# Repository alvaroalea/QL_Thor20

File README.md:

# THOR PC Computer (Compatible with Sinclair Ql)
A reverse engineering exercice using the Sinclair QL compatible Thor-20 Computer as target

Licensed under Cern OHL-S - https://ohwr.org/cern_ohl_s_v2.txt

## WARNING: DO NOT USE THIS PROJECT IS NOT TESTED AND MISSING THINGS
This is not a functional item, it's only a exercice of reverse engineering to reinforce my skills in Kicad EDA Software.

## History

With the end of the comercial life of the Sinclair QL, other companies fill the gap, CST create several models of the Thor computer.

The subject of this project is a interesting one, using old stock of original QL boards, and a re-edition of several of the previous expansion board together with a fancy desktop case to make a enhaced QL Computer, so the Thor consist of:

- The Original QL Board
- The RAM + ROM expansion board board (512Kb of RAM)
- The CST Floppy Disk Interface with 1 or 2 3 1/2" floppy drivers
- The CST SCSI Disk Interface
- The mICE mouse + desktop software solution
- A RTC implementation
- A fancy box
- A upgraded in-box power supply
- Standar PC XT Interface

This was called Thor PC, Thor 1 or Thor 8, depend of the sources of information, there are 3 version available, 1F, 2F, 2WF depend on the number of floppys and Winchister hard disc or not, 1F,2F do not incorporate the IC of the SCSI interface, but can be upgraded later.

Later, CST upgrade it and made the Thor 20 and Thor 21, this was Thor 1 with a CPU-Addon card, that include a 68020 CPU at 12 or 16Mhz, and a 68881 FPU math coprocesor.

Unfortunately, the use of the original QL board, and the RAM in 8bits, cause this board to be only twice the speed of the original QL, while a Gold Card provide the same with twice the ram, and the Super Gold Card provide 4 times the speed of the QL, 4Mb of RAM using the same microprocessor.

## The Project

I will try to recreate all the hardware, and document in a proper way everything I can get of the Thor Computer, up to day there is only some low resolution pictures, a bad scanned service manual, and a dump of some of the ROMs of the computer.

## Technical Information

### Power Supply
The thor 20 come with a IEC C13 socket in the back, and a secondary C14 (for the monitor) a switch shall power on/off both the computer and monitor.

Internally a power supply rated to 30W is used for the system. it provide:
- +5Vdc probably at 3A (for everything)
- +12Vdc probably at 1A (for QL, hard disc and floppy)
- -12Vdc probably at 250mA (for the serial ports of the QL)

a MeanWell PT-45A is probably the good replacement ( https://www.meanwell-web.com/en-gb/ac-dc-triple-output-open-frame-power-supply-output-pt--45a ).

### SCSI Upgrade Kit
To upgrade the Thor 1F or 2F to 2WF a kit of IC11,IC12,IC13 and IC15 can be installed to enable the SCSI interface.

### Memory Mapping

- 0000-0048 Sinclair QL ROM
- 0049-0064 Free for ROM Cartridge Slot
- 0065-0096 Internal 32Kb I/O
- 0097-0128 Free but reserved for I/O
- 0129-0256 Internal QL 128K RAM including Video ram
- 0257-0768 CST 512 Kb Expansion RAM
- 0769-0832 Free 64Kb for external expansion interfaces
- 0833-0999 5x32Kb + 1x8Kb expasion ROM
- 1000-1024 CST Expansion I/O

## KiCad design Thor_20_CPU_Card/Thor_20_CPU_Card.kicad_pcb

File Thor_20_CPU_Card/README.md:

# CST Thor - 68020 CPU Board.

(C) 2023 Alvaro Alea Fernandez

License under: CERN Open Hardware Licence Version 2 - Strongly Reciprocal

https://ohwr.org/cern_ohl_s_v2.txt

This board is the "overdrive" board that shall upgrade the 68008 processor of the Sinclair QL to a 68020 one.

THIS BOARD HAS NOT BEEN TESTED!! Use at your own risk.

##Information

There at least 1 GAL and 1 ROM with ecuations or contens are missing so it not usable at present.

* Get energy from diferent a power supply.
* Dimensions are not checked, there is mismatch in pictures.
* Schematic is not pretty, but is enought to be able to do the PCB.

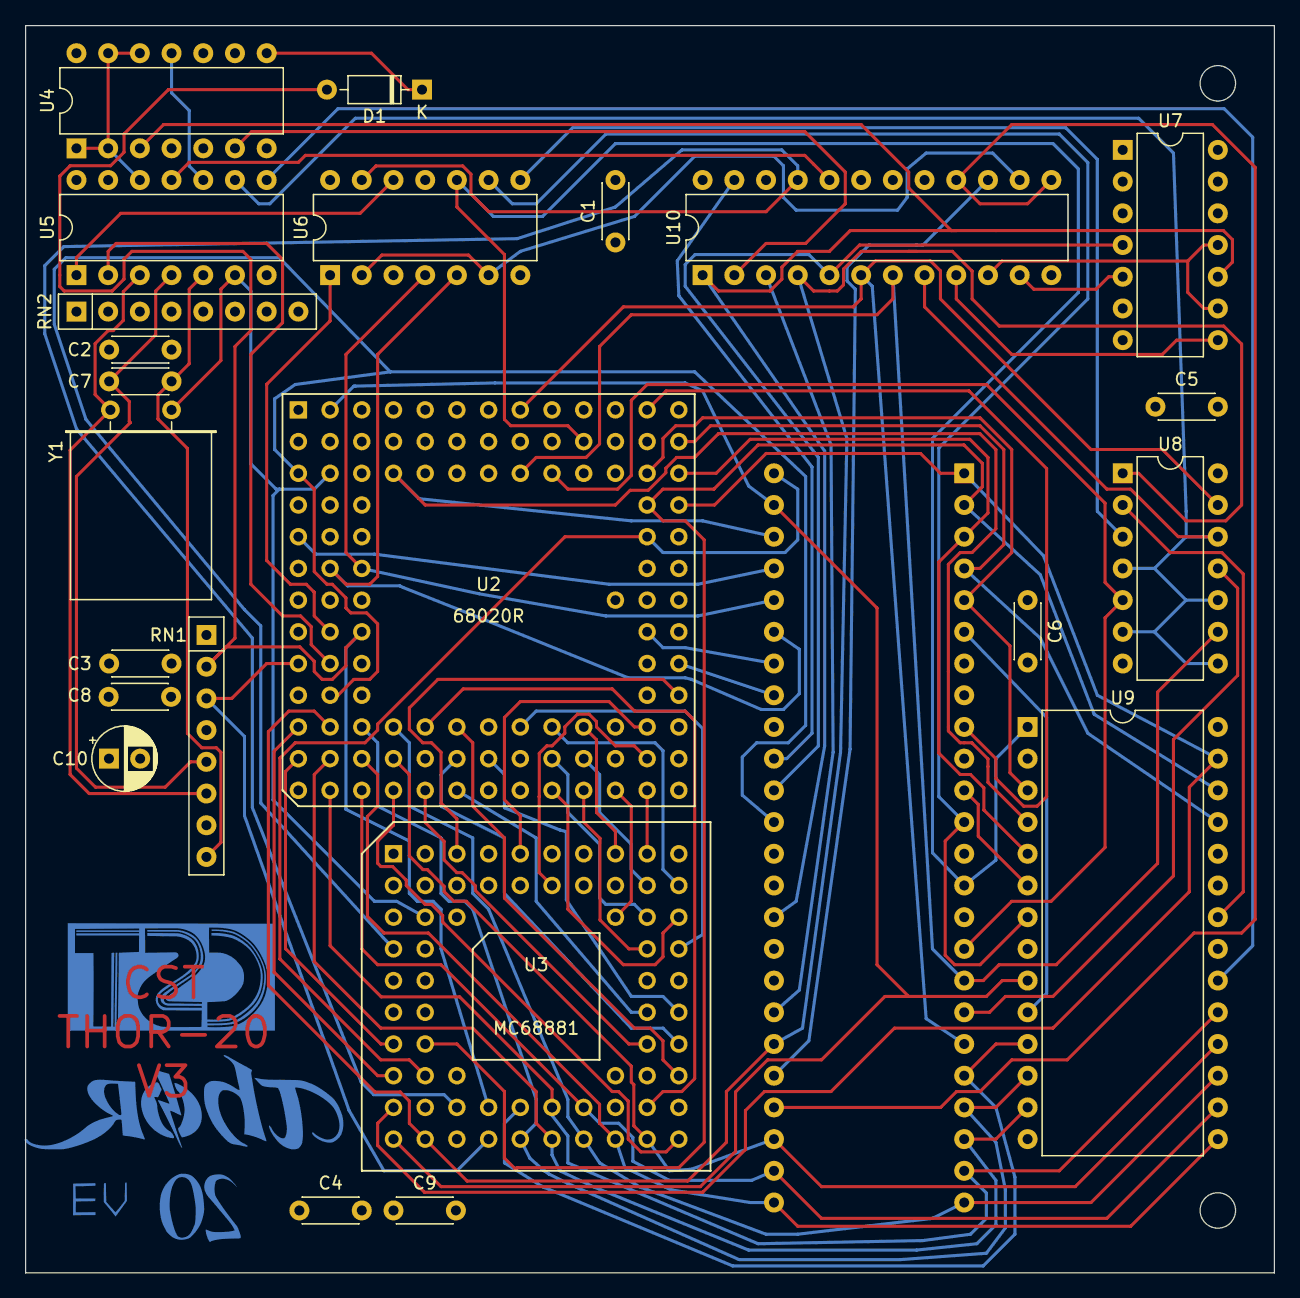
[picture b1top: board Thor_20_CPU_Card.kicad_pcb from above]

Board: 4 copper layers, 100.0 x 99.9 mm, 24 parts (1 on the bottom side), 92 nets.

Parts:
C1, C2, C3, C4, C5, C6, C7, C8, C9: C; C_Disc_D4.3mm_W1.9mm_P5.00mm
C10: C_Polarized; CP_Radial_D5.0mm_P2.50mm
D1: BAT85; D_DO-35_SOD27_P7.62mm_Horizontal
RN1, RN2: R_Pack04_SIP_Split; R_Array_SIP8
U1: 68008D; DIP-48_W15.24mm
U2: 68020R; PGA114
U3: MC68881; PGA68
U4: 74LS74; DIP-14_W7.62mm
U5: 74LS04; DIP-14_W7.62mm
U6: 74LS11; DIP-14_W7.62mm
U7: 74LS290; DIP-14_W7.62mm
U8: 74LS05; DIP-14_W7.62mm
U9: W27C512; DIP-28_W15.24mm
U10: PAL20R4; DIP-24_W7.62mm
Y1: 12Mhz; Crystal_HC18-U_Horizontal

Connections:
+5V: C1.1, C2.1, C3.1, C4.1, C5.1, C6.1, C8.1, C10.1, RN1.1 (R1.1), RN1.4 (R2.2), RN2.2 (R1.2), U1.13 (VCC), U2.A1 (BGACK), U2.A9 (VCC), U2.B3 (BR), U2.D1 (VCC), U2.D2 (VCC), U2.D3 (VCC), U2.E3 (VCC), U2.G11 (VCC), U2.G13 (VCC), U2.H1 (CDIS), U2.J12 (IPL0), U2.M8 (VCC), U2.N8 (VCC), U2.N13 (VCC), U3.A1 (VDD), U3.B1 (VDD), U3.B8 (VDD), U3.E2 (VDD), U3.E9 (VDD), U3.F1 (~SIZE), U3.H3 (A0), U3.H8 (VDD), U3.J2 (VDD), U4.4 (~S), U4.10 (~S), U4.14 (VCC), U5.14 (VCC), U6.11, U6.14 (VCC), U7.14 (VCC), U8.14 (VCC), U9.28 (VCC), U10.24 (VCC)
/A0: U1.46 (A0), U2.C4 (A0), U9.4 (A6)
/A1: U1.47 (A1), U2.A2 (A1), U3.K1 (A1), U9.9 (A1)
/A2: U1.48 (A2), U2.E12 (A2), U3.H2 (A2), U9.8 (A2)
/A3: U1.1 (A3), U2.D13 (A3), U3.J1 (A3), U9.27 (A14)
/A4: U1.2 (A4), U2.D12 (A4), U3.G2 (A4), U9.26 (A13)
/A5: U1.3 (A5), U2.C13 (A5), U9.5 (A5)
/A6: U1.4 (A6), U2.B13 (A6), U9.25 (A8)
/A7: U1.5 (A7), U2.C12 (A7), U9.3 (A7)
/A8: U1.6 (A8), U2.A13 (A8), U9.10 (A0)
/A9: U1.7 (A9), U2.C11 (A9), U9.24 (A9)
/A10: U1.8 (A10), U2.B12 (A10), U9.21 (A10)
/A11: U1.9 (A11), U2.A12 (A11), U9.23 (A11)
/A12: U1.10 (A12), U2.C10 (A12), U9.2 (A12)
/A13: U1.11 (A13), U2.B11 (A13), U9.6 (A4)
/A14: U1.12 (A14), U2.A11 (A14), U6.9, U9.7 (A3)
/A15: U1.14 (A15), U2.B10 (A15), U6.10, U9.1 (A15)
/A16: U1.16 (A16), U2.C9 (A16), U8.5
/A17: U1.17 (A17), U2.C8 (A17), U8.9, U10.7 (I7)
/A18: U1.18 (A18), U2.B8 (A18), U8.11
/A19: U1.19 (A19), U2.A8 (A19), U8.13, U10.6 (I6)
/ACK2: U5.11, U10.20 (I04)
/AS: U2.L1 (AS), U3.H1 (~AS), U5.13
/AS2: U4.6 (~Q), U10.2 (I2)
/AS_68K8: U1.28 (AS), U10.13 (I12), U10.16 (IO8)
/AVEC: U2.H2 (AVEC), U6.1, U10.22 (IO2)
/BERR: U2.J2 (BERR), U5.2
/CLK: RN1.7 (R4.1), U2.C2 (CLK), U3.C2 (CLK), U5.6, Y1.2
/CLK_68K8: U1.34 (CLK), U4.3 (C), U7.10 (Cp0), U10.1 (I1/CLK)
/CPU: U6.2, U6.6, U10.14 (IO10)
/D0: U2.K13 (D0), U3.A3 (D0)
/D1: U2.K12 (D1), U3.A4 (D1)
/D2: U2.L13 (D2), U3.B5 (D2)
/D3: U2.L12 (D3), U3.A5 (D3)
/D4: U2.M13 (D4), U3.A6 (D4)
/D5: U2.M12 (D5), U3.B6 (D5)
/D6: U2.M11 (D6), U3.A7 (D6)
/D7: U2.L10 (D7), U3.A8 (D7)
/D8: U2.N12 (D8), U3.A9 (D8)
/D9: U2.N11 (D9), U3.C8 (D9)
/D10: U2.M10 (D10), U3.B9 (D10)
/D11: U2.L9 (D11), U3.B10 (D11)
/D12: U2.N10 (D12), U3.D9 (D12)
/D13: U2.M9 (D13), U3.C9 (D13)
/D14: U2.N9 (D14), U3.C10 (D14)
/D15: U2.L8 (D15), U3.D10 (D15)
/D16: U2.M7 (D16), U3.F10 (D16)
/D17: U2.N6 (D17), U3.F9 (D17)
/D18: U2.M6 (D18), U3.G10 (D18)
/D19: U2.L6 (D19), U3.H10 (D19)
/D20: U2.N5 (D20), U3.G9 (D20)
/D21: U2.M5 (D21), U3.J10 (D21)
/D22: U2.N4 (D22), U3.K10 (D22)
/D23: U2.L5 (D23), U3.J9 (D23)
/D24: U1.27 (D0), U2.M4 (D24), U3.K9 (D24), U9.18 (D6)
/D25: U1.26 (D1), U2.N3 (D25), U3.J7 (D25), U9.16 (D4)
/D26: U1.25 (D2), U2.M3 (D26), U3.K8 (D26), U9.15 (D3)
/D27: U1.24 (D3), U2.L4 (D27), U3.K7 (D27), U9.17 (D5)
/D28: U1.23 (D4), U2.N2 (D28), U3.J6 (D28), U9.19 (D7)
/D29: U1.22 (D5), U2.M2 (D29), U3.K6 (D29), U9.13 (D2)
/D30: U1.21 (D6), U2.L3 (D30), U3.K5 (D30), U9.12 (D1)
/D31: U1.20 (D7), U2.N1 (D31), U3.J5 (D31), U9.11 (D0)
/DS: U2.M1 (DS), U3.G1 (~DS)
/DSACK0: D1.2 (A), RN1.2 (R1.2), U2.H3 (DSACK0), U3.J4 (~DSACK0)
/DSACK1: RN1.3 (R2.1), U2.J1 (DSACK1), U3.K4 (~DSACK1)
/DS_68K8: U1.29 (DS), U10.15 (IO9)
/DTACK_68K8: U1.31 (DTACK), U10.3 (I3)
/EPROM: RN2.1 (R1.1), U5.9, U8.4, U8.6, U8.8, U8.10, U8.12, U10.8 (I8)
/E_68K8: U1.38 (E), U7.4 (Q2), U10.5 (I5)
/FC0: U1.45 (FC0), U2.E1 (FC0), U6.3
/FC1: U1.44 (FC1), U2.F3 (FC1), U6.4
/FC2: U1.43 (FC2), U2.F2 (FC2), U6.5
/FPU_CS: U3.J3 (~CS), U6.13, U10.21 (IO3)
/IPL1: U1.41 (IPL1), U2.J13 (IPL1)
/IPL2: U1.42 (IPL0/2), U2.H12 (IPL2)
/RESET: C9.1, U1.37 (RESET), U2.C1 (RESET), U2.K2 (HALT), U3.D1 (~RESET)
/ROM_CS: U5.8, U9.20 (~CE)
/RW: U1.30 (R/W), U2.L2 (R/W), U3.K2 (R/~W), U8.1, U10.4 (I4/PD)
/VPA_68K8: U1.39 (VPA), U10.23 (IO1)
GND: C1.2, C2.2, C3.2, C4.2, C5.2, C6.2, C8.2, C9.2, C10.2, U1.15 (GND), U1.35 (GND), U2.A10 (GND), U2.B1 (GND), U2.B9 (GND), U2.C3 (GND), U2.F12 (GND), U2.G12 (GND), U2.H13 (GND), U2.J3 (GND), U2.K1 (GND), U2.K3 (GND), U2.L7 (GND), U2.L11 (GND), U2.N7 (GND), U3.A2 (VSS), U3.A10 (VSS), U3.B2 (VSS), U3.B3 (VSS), U3.B4 (/SENSE), U3.B7 (VSS), U3.C1 (VSS), U3.C3 (VSS), U3.D2 (VSS), U3.E10 (VSS), U3.F2 (VSS), U3.H9 (VSS), U3.J8 (VSS), U3.K3 (VSS), U4.7 (GND), U5.7 (GND), U6.7 (GND), U7.1 (Ms1), U7.3 (Ms2), U7.7 (GND), U7.12 (Mr1), U7.13 (Mr2), U8.7 (GND), U9.14 (GND), U10.12 (GND)
unnamed: D1.1 (K), U4.8 (~Q)
unnamed: C7.1, RN1.5 (R3.1), U5.4
unnamed: RN1.6 (R3.2), U5.3, Y1.1
unnamed: C7.2, RN1.8 (R4.2), U5.5
unnamed: U4.1 (~R), U4.2 (D), U4.12 (D), U4.13 (~R), U5.12
unnamed: U4.11 (C), U5.10
unnamed: U5.1, U6.12
unnamed: U6.8, U8.3
unnamed: U8.2, U9.22 (~OE/Vpp)
unnamed: U7.8 (Q3), U10.9 (I9)
unnamed: U7.9 (Q0), U7.11 (Cp1), U10.10 (I10)
unnamed: U7.5 (Q1), U10.11 (I11)

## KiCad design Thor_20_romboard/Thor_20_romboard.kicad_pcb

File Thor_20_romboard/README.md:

# CST Thor - ROM Board.

(C) 2023 Alvaro Alea Fernandez

License under: CERN Open Hardware Licence Version 2 - Strongly Reciprocal

https://ohwr.org/cern_ohl_s_v2.txt

This board has been reverse engineered from pictures freely available on internet.

THIS BOARD HAS NOT BEEN TESTED!! Use at your own risk.

This is a fast hack, not real dimension or position or tracks.

## Technical Details

The board has space for 6 IC Eprom Memories.
The schematic depend on 2 lines of selection, one is A15 or /A15, and the other come from IC5  and decode the A16,A17 lines, that mean that is targeted for the 6 32Kb IC, (type 27C256) and will use the 0xB0000 to 0xF8FFF leaving the 0xA0000 to 0xAFFFF empty to be used by the expansion slot on the back of the computer. in any case 0xF9000 to 0xFFFFF (last 24kb of memory) is reserved for I/O

Complete decode of the memory space depend of pin 13 of IC4 (BLK0) a programable GAL, so it's unknow, but not expected to have any spacial mapping or shadowing.

From factory, Thor come with 2 socket used and 4 free:

The Thor system rom consist on 40Kb divided in two IC:
- IC6 a 27C64, 8Kb, some pictures has a sticker "Thor" and a date
- IC5 a 27C256, 32Kb, some pictures has a stickers with a version number, Thor20Sysrom (from 4.11 to 5.22 can be found on Dilwin pages)

IC 1-4 are free for other used, and are interchangables:
- IC4 a 27C256, 32Kb, it has sticker with "Speed Screen (C) 1988 CST" (4.23 can be found in thor820roms.zip on Dilwin pages)
- IC3 a 27C256, 32Kb, it has sticker with "Int ROM 0952" InterLogic Extension package (2.10 cann be found in thor820roms.zip on Dilwin pages)
- IC2,IC1 type 27C256, 32Kb, its show in some pictures unpopulated, and in others with a "1","2", o "3" (for IC3) stickers, it's not clear the contents, but is expected that can be ROM for compiler or other kind of toolkit for the QL

Usually ROM Toolkit for QL area 16Kb, it's not clear if Thor ROM inicializate all posible 16Kb blocks, or requiered a user inicialization, or if there is a diferent mechanism to inicializate it.

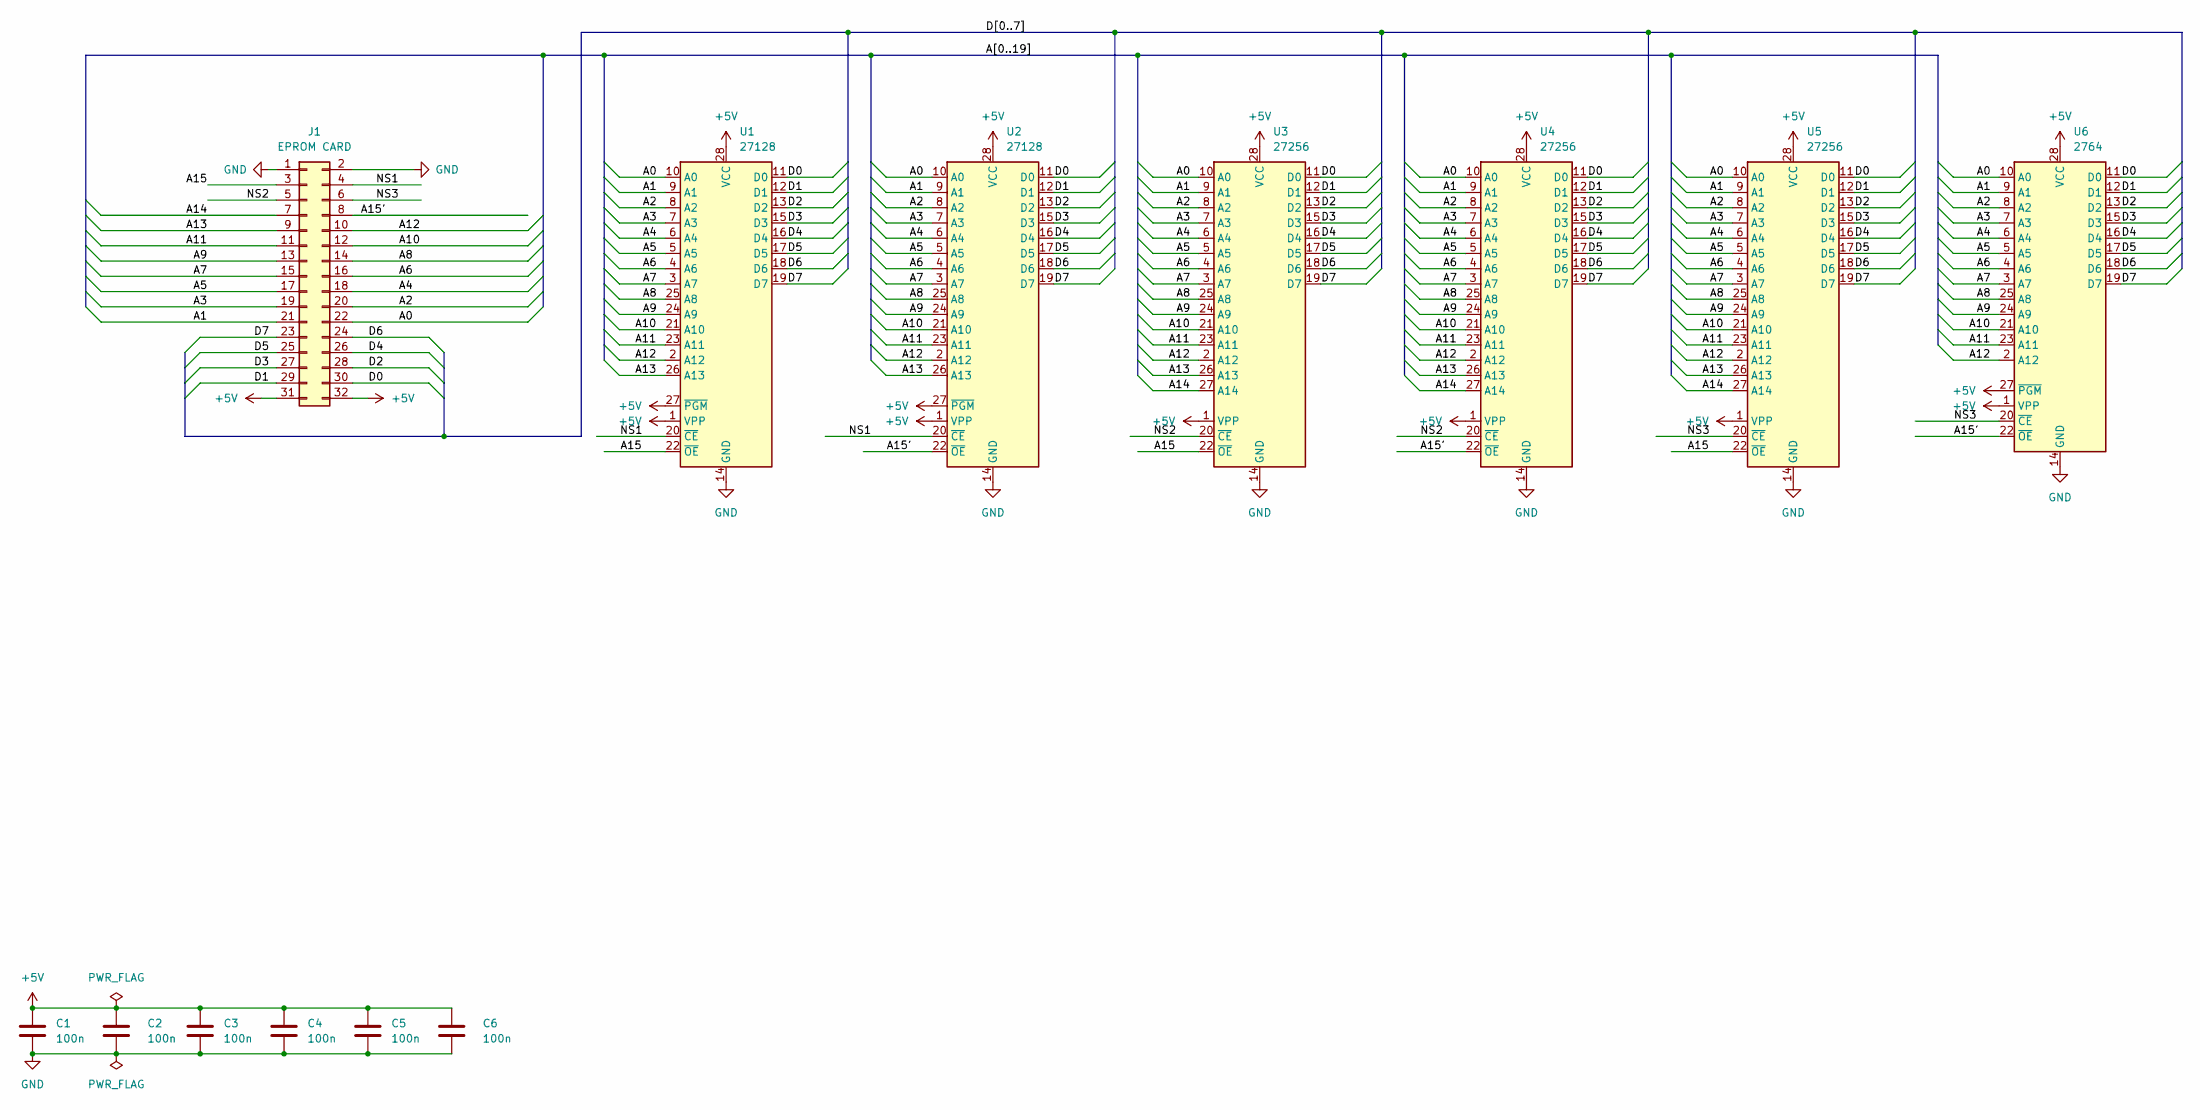
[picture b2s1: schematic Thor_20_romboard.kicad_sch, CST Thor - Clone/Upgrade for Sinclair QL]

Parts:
C1, C2, C3, C4, C5, C6: 100n; C_Disc_D4.3mm_W1.9mm_P5.00mm
J1: EPROM CARD; PinSocket_2x16_P2.54mm_Horizontal
U1, U2: 27128; DIP-28_W15.24mm
U3, U4, U5: 27256; DIP-28_W15.24mm
U6: 2764; DIP-28_W15.24mm

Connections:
+5V: C1.1, C2.1, C3.1, C4.1, C5.1, C6.1, J1.31, J1.32, U1.1 (VPP), U1.27 (~PGM), U1.28 (VCC), U2.1 (VPP), U2.27 (~PGM), U2.28 (VCC), U3.1 (VPP), U3.28 (VCC), U4.1 (VPP), U4.28 (VCC), U5.1 (VPP), U5.28 (VCC), U6.1 (VPP), U6.27 (~PGM), U6.28 (VCC)
/A0: J1.22, U1.10 (A0), U2.10 (A0), U3.10 (A0), U4.10 (A0), U5.10 (A0), U6.10 (A0)
/A1: J1.21, U1.9 (A1), U2.9 (A1), U3.9 (A1), U4.9 (A1), U5.9 (A1), U6.9 (A1)
/A2: J1.20, U1.8 (A2), U2.8 (A2), U3.8 (A2), U4.8 (A2), U5.8 (A2), U6.8 (A2)
/A3: J1.19, U1.7 (A3), U2.7 (A3), U3.7 (A3), U4.7 (A3), U5.7 (A3), U6.7 (A3)
/A4: J1.18, U1.6 (A4), U2.6 (A4), U3.6 (A4), U4.6 (A4), U5.6 (A4), U6.6 (A4)
/A5: J1.17, U1.5 (A5), U2.5 (A5), U3.5 (A5), U4.5 (A5), U5.5 (A5), U6.5 (A5)
/A6: J1.16, U1.4 (A6), U2.4 (A6), U3.4 (A6), U4.4 (A6), U5.4 (A6), U6.4 (A6)
/A7: J1.15, U1.3 (A7), U2.3 (A7), U3.3 (A7), U4.3 (A7), U5.3 (A7), U6.3 (A7)
/A8: J1.14, U1.25 (A8), U2.25 (A8), U3.25 (A8), U4.25 (A8), U5.25 (A8), U6.25 (A8)
/A9: J1.13, U1.24 (A9), U2.24 (A9), U3.24 (A9), U4.24 (A9), U5.24 (A9), U6.24 (A9)
/A10: J1.12, U1.21 (A10), U2.21 (A10), U3.21 (A10), U4.21 (A10), U5.21 (A10), U6.21 (A10)
/A11: J1.11, U1.23 (A11), U2.23 (A11), U3.23 (A11), U4.23 (A11), U5.23 (A11), U6.23 (A11)
/A12: J1.10, U1.2 (A12), U2.2 (A12), U3.2 (A12), U4.2 (A12), U5.2 (A12), U6.2 (A12)
/A13: J1.9, U1.26 (A13), U2.26 (A13), U3.26 (A13), U4.26 (A13), U5.26 (A13)
/A14: J1.7, U3.27 (A14), U4.27 (A14), U5.27 (A14)
/A15: J1.3, U1.22 (~OE), U3.22 (~OE), U5.22 (~OE)
/A15': J1.8, U2.22 (~OE), U4.22 (~OE), U6.22 (~OE)
/D0: J1.30, U1.11 (D0), U2.11 (D0), U3.11 (D0), U4.11 (D0), U5.11 (D0), U6.11 (D0)
/D1: J1.29, U1.12 (D1), U2.12 (D1), U3.12 (D1), U4.12 (D1), U5.12 (D1), U6.12 (D1)
/D2: J1.28, U1.13 (D2), U2.13 (D2), U3.13 (D2), U4.13 (D2), U5.13 (D2), U6.13 (D2)
/D3: J1.27, U1.15 (D3), U2.15 (D3), U3.15 (D3), U4.15 (D3), U5.15 (D3), U6.15 (D3)
/D4: J1.26, U1.16 (D4), U2.16 (D4), U3.16 (D4), U4.16 (D4), U5.16 (D4), U6.16 (D4)
/D5: J1.25, U1.17 (D5), U2.17 (D5), U3.17 (D5), U4.17 (D5), U5.17 (D5), U6.17 (D5)
/D6: J1.24, U1.18 (D6), U2.18 (D6), U3.18 (D6), U4.18 (D6), U5.18 (D6), U6.18 (D6)
/D7: J1.23, U1.19 (D7), U2.19 (D7), U3.19 (D7), U4.19 (D7), U5.19 (D7), U6.19 (D7)
/NS1: J1.4, U1.20 (~CE), U2.20 (~CE)
/NS2: J1.5, U3.20 (~CE), U4.20 (~CE)
/NS3: J1.6, U5.20 (~CE), U6.20 (~CE)
GND: C1.2, C2.2, C3.2, C4.2, C5.2, C6.2, J1.1, J1.2, U1.14 (GND), U2.14 (GND), U3.14 (GND), U4.14 (GND), U5.14 (GND), U6.14 (GND)

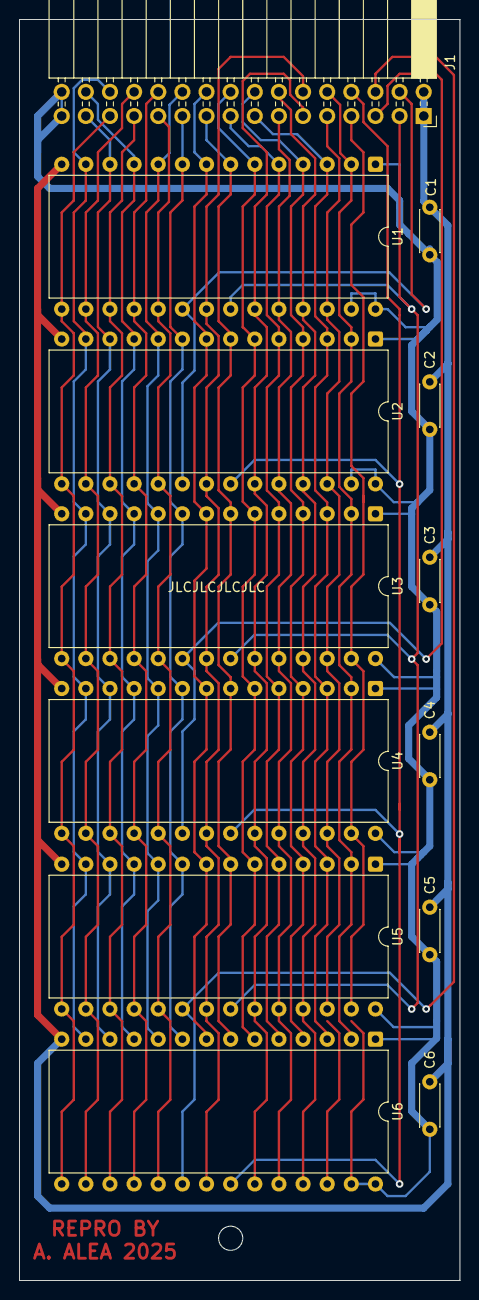
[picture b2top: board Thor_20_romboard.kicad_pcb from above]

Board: 2 copper layers, 46.4 x 132.7 mm, 13 parts (0 on the bottom side), 30 nets.

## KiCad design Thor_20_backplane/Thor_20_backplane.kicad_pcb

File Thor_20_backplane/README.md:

# CST Thor - Original Backplane.

(C) 2023 Alvaro Alea Fernandez

License under: CERN Open Hardware Licence Version 2 - Strongly Reciprocal

https://ohwr.org/cern_ohl_s_v2.txt

This board has been reverse engineered from pictures freely available on internet.

THIS BOARD HAS NOT BEEN TESTED!! Use at your own risk.

##Information

This backplane is a replacement of the original that come with Thor PC Computer,
intended for install the QL main board in a case along with the CST expansion board of the Thor Computer.

* Get energy from diferent a power supply.
* Dimensions are not checked, there is mismatch in pictures.
* Schematic is not pretty, but is enought to be able to do the PCB.

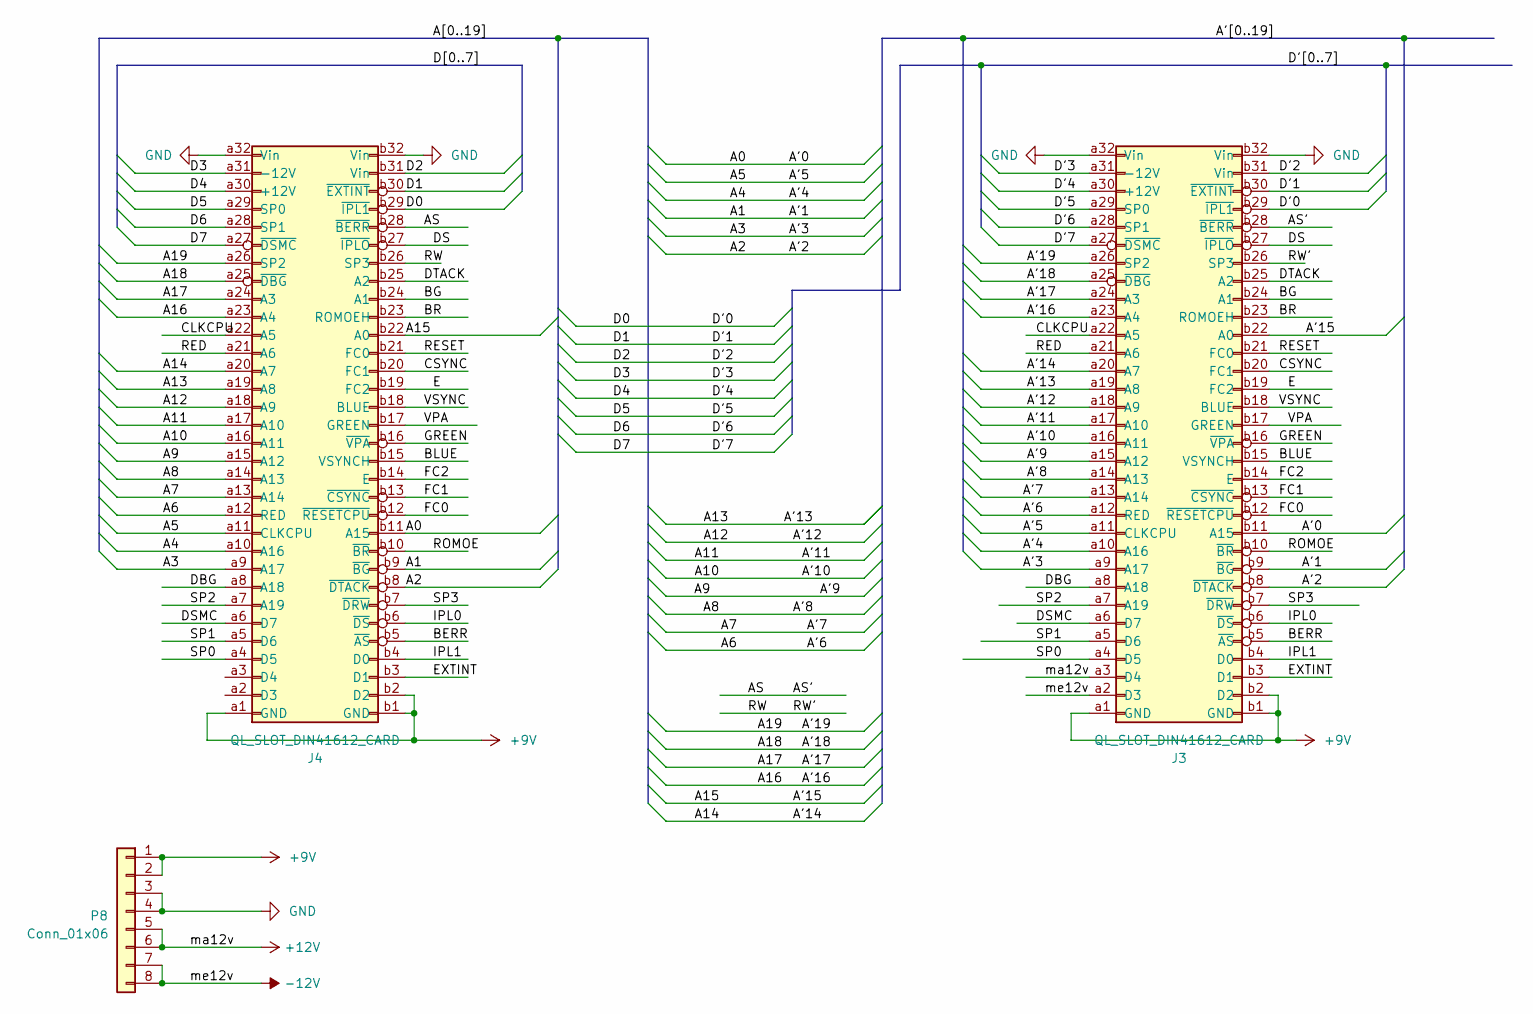
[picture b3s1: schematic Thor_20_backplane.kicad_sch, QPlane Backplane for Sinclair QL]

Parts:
J3, J4: QL_SLOT_DIN41612_CARD; DIN41612_B_2x32_Male_Vertical_THT
P8: Conn_01x06; PinHeader_1x08_P2.54mm_Vertical

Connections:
+9V: J3.a1 (GND), J3.b1 (GND), J3.b2 (D2), J4.a1 (GND), J4.b1 (GND), J4.b2 (D2), P8.1, P8.2
+12V: J3.a3 (D4), P8.5, P8.6
-12V: J3.a2 (D3), P8.7, P8.8
/A0: J3.b11 (A15), J4.b11 (A15)
/A1: J3.b9 (~BG), J4.b9 (~BG)
/A2: J3.b8 (~DTACK), J4.b8 (~DTACK)
/A3: J3.a9 (A17), J4.a9 (A17)
/A4: J3.a10 (A16), J4.a10 (A16)
/A5: J3.a11 (CLKCPU), J4.a11 (CLKCPU)
/A6: J3.a12 (RED), J4.a12 (RED)
/A7: J3.a13 (A14), J4.a13 (A14)
/A8: J3.a14 (A13), J4.a14 (A13)
/A9: J3.a15 (A12), J4.a15 (A12)
/A10: J3.a16 (A11), J4.a16 (A11)
/A11: J3.a17 (A10), J4.a17 (A10)
/A12: J3.a18 (A9), J4.a18 (A9)
/A13: J3.a19 (A8), J4.a19 (A8)
/A14: J3.a20 (A7), J4.a20 (A7)
/A15: J3.b22 (A0), J4.b22 (A0)
/A16: J3.a23 (A4), J4.a23 (A4)
/A17: J3.a24 (A3), J4.a24 (A3)
/A18: J3.a25 (~DBG), J4.a25 (~DBG)
/A19: J3.a26 (SP2), J4.a26 (SP2)
/AS: J3.b28 (~BERR), J4.b28 (~BERR)
/BERR: J3.b5 (~AS), J4.b5 (~AS)
/BG: J3.b24 (A1), J4.b24 (A1)
/BLUE: J3.b15 (VSYNCH), J4.b15 (VSYNCH)
/BR: J3.b23 (ROMOEH), J4.b23 (ROMOEH)
/CLKCPU: J3.a22 (A5), J4.a22 (A5)
/CSYNC: J3.b20 (FC1), J4.b20 (FC1)
/D0: J3.b29 (~IPL1), J4.b29 (~IPL1)
/D1: J3.b30 (~EXTINT), J4.b30 (~EXTINT)
/D2: J3.b31 (Vin), J4.b31 (Vin)
/D3: J3.a31 (-12V), J4.a31 (-12V)
/D4: J3.a30 (+12V), J4.a30 (+12V)
/D5: J3.a29 (SP0), J4.a29 (SP0)
/D6: J3.a28 (SP1), J4.a28 (SP1)
/D7: J3.a27 (~DSMC), J4.a27 (~DSMC)
/DBG: J3.a8 (A18), J4.a8 (A18)
/DS: J3.b27 (~IPLO), J4.b27 (~IPLO)
/DSMC: J3.a6 (D7), J4.a6 (D7)
/DTACK: J3.b25 (A2), J4.b25 (A2)
/E: J3.b19 (FC2), J4.b19 (FC2)
/EXTINT: J3.b3 (D1), J4.b3 (D1)
/FC0: J3.b12 (~RESETCPU), J4.b12 (~RESETCPU)
/FC1: J3.b13 (~CSYNC), J4.b13 (~CSYNC)
/FC2: J3.b14 (E), J4.b14 (E)
/GREEN: J3.b16 (~VPA), J4.b16 (~VPA)
/IPL0: J3.b6 (~DS), J4.b6 (~DS)
/IPL1: J3.b4 (D0), J4.b4 (D0)
/RED: J3.a21 (A6), J4.a21 (A6)
/RESET: J3.b21 (FC0), J4.b21 (FC0)
/ROMOE: J3.b10 (~BR), J4.b10 (~BR)
/RW: J3.b26 (SP3), J4.b26 (SP3)
/SP0: J3.a4 (D5), J4.a4 (D5)
/SP1: J3.a5 (D6), J4.a5 (D6)
/SP2: J3.a7 (A19), J4.a7 (A19)
/SP3: J3.b7 (~DRW), J4.b7 (~DRW)
/VPA: J3.b17 (GREEN), J4.b17 (GREEN)
/VSYNC: J3.b18 (BLUE), J4.b18 (BLUE)
GND: J3.a32 (Vin), J3.b32 (Vin), J4.a32 (Vin), J4.b32 (Vin), P8.3, P8.4

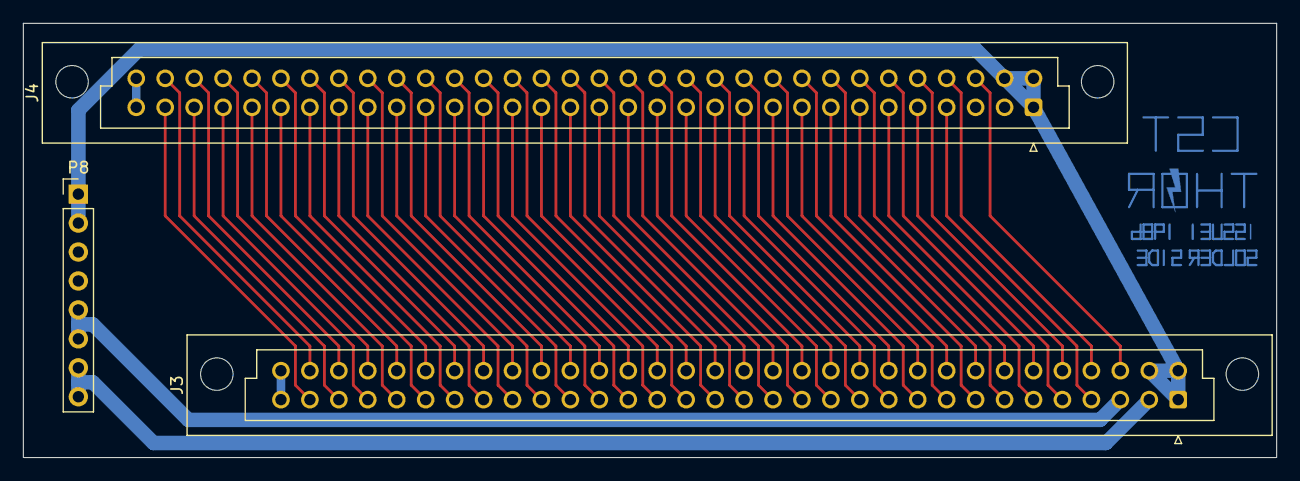
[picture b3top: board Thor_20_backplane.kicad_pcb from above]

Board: 2 copper layers, 110.0 x 38.1 mm, 3 parts (0 on the bottom side), 61 nets.

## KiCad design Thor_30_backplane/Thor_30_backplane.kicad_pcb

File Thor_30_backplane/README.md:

# CST Thor - Alternative Backplane.

(C) 2023 Alvaro Alea Fernandez

License under: CERN Open Hardware Licence Version 2 - Strongly Reciprocal

https://ohwr.org/cern_ohl_s_v2.txt

This board is a FANTASY board that shall allow to install a QL board with standar interfaces in a Thor case.

THIS BOARD HAS NOT BEEN TESTED!! Use at your own risk.

##Information

intended for install the QL main board in a case along with memory, trump card, CST Disk or other expansion boards of the Sinclair QL Computer.

* Get energy from diferent a power supply.
* Dimensions are not checked, there is mismatch in pictures.
* Schematic is not pretty, but is enought to be able to do the PCB.

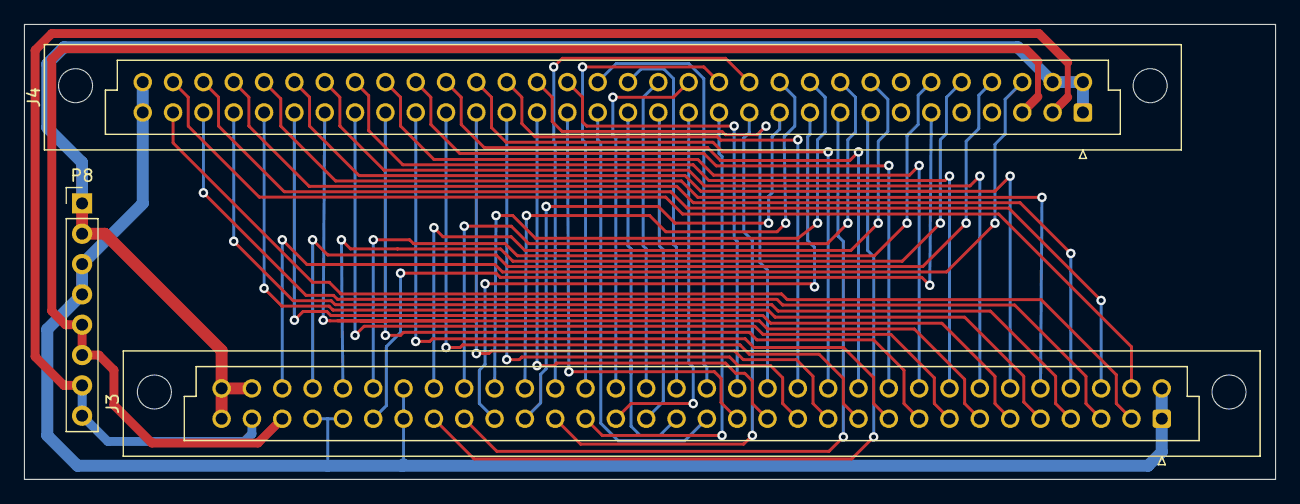
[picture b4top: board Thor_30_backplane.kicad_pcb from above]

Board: 2 copper layers, 104.8 x 38.1 mm, 3 parts (0 on the bottom side), 57 nets.

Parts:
J3: BOARDS_SLOT_DIN41612_CARD; DIN41612_B_2x32_Male_Vertical_THT
J4: QL_SLOT_DIN41612_CARD; DIN41612_B_2x32_Male_Vertical_THT
P8: Conn_01x06; PinHeader_1x08_P2.54mm_Vertical

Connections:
+5V: J3.a32 (Vin), J3.b31 (Vin), J3.b32 (Vin), J4.a1 (GND), J4.b1 (GND), J4.b2 (D2), P8.1, P8.2
+12V: J3.a30 (+12V), J4.a3 (D4), P8.5, P8.6
-12V: J3.a31 (-12V), J4.a2 (D3), P8.7, P8.8
/A0: J3.b22 (A0), J4.b11 (A15)
/A1: J3.b24 (A1), J4.b9 (~BG)
/A2: J3.b25 (A2), J4.b8 (~DTACK)
/A3: J3.a24 (A3), J4.a9 (A17)
/A4: J3.a23 (A4), J4.a10 (A16)
/A5: J3.a22 (A5), J4.a11 (CLKCPU)
/A6: J3.a21 (A6), J4.a12 (RED)
/A7: J3.a20 (A7), J4.a13 (A14)
/A8: J3.a19 (A8), J4.a14 (A13)
/A9: J3.a18 (A9), J4.a15 (A12)
/A10: J3.a17 (A10), J4.a16 (A11)
/A11: J3.a16 (A11), J4.a17 (A10)
/A12: J3.a15 (A12), J4.a18 (A9)
/A13: J3.a14 (A13), J4.a19 (A8)
/A14: J3.a13 (A14), J4.a20 (A7)
/A15: J3.b11 (A15), J4.b22 (A0)
/A16: J3.a10 (A16), J4.a23 (A4)
/A17: J3.a9 (A17), J4.a24 (A3)
/A18: J3.a8 (A18), J4.a25 (~DBG)
/A19: J3.a7 (A19), J4.a26 (SP2)
/AS: J3.b5 (~AS), J4.b28 (~BERR)
/BERR: J3.b28 (~BERR), J4.b5 (~AS)
/BG: J3.b9 (~BG), J4.b24 (A1)
/BLUE: J3.b18 (BLUE), J4.b15 (VSYNCH)
/BR: J3.b10 (~BR), J4.b23 (ROMOEH)
/CLKCPU: J3.a11 (CLKCPU), J4.a22 (A5)
/CSYNC: J3.b13 (~CSYNC), J4.b20 (FC1)
/D0: J3.b4 (D0), J4.b29 (~IPL1)
/D1: J3.b3 (D1), J4.b30 (~EXTINT)
/D2: J3.b2 (D2), J4.b31 (Vin)
/D3: J3.a2 (D3), J4.a31 (-12V)
/D4: J3.a3 (D4), J4.a30 (+12V)
/D5: J3.a4 (D5), J4.a29 (SP0)
/D6: J3.a5 (D6), J4.a28 (SP1)
/D7: J3.a6 (D7), J4.a27 (~DSMC)
/DBG: J3.a25 (~DBG), J4.a8 (A18)
/DS: J3.b6 (~DS), J4.b27 (~IPLO)
/DSMC: J3.a27 (~DSMC), J4.a6 (D7)
/DTACK: J3.b8 (~DTACK), J4.b25 (A2)
/E: J3.b14 (E), J4.b19 (FC2)
/EXTINT: J3.b30 (~EXTINT), J4.b3 (D1)
/FC0: J3.b21 (FC0), J4.b12 (~RESETCPU)
/FC1: J3.b20 (FC1), J4.b13 (~CSYNC)
/FC2: J3.b19 (FC2), J4.b14 (E)
/GREEN: J3.b17 (GREEN), J4.b16 (~VPA)
/IPL0: J3.b27 (~IPLO), J4.b6 (~DS)
/IPL1: J3.b29 (~IPL1), J4.b4 (D0)
/RED: J3.a12 (RED), J4.a21 (A6)
/RESET: J3.b12 (~RESETCPU), J4.b21 (FC0)
/ROMOE: J3.b23 (ROMOEH), J4.b10 (~BR)
/RW: J3.b7 (~DRW), J4.b26 (SP3)
/VPA: J3.b16 (~VPA), J4.b17 (GREEN)
/VSYNC: J3.b15 (VSYNCH), J4.b18 (BLUE)
GND: J3.a1 (GND), J3.a26 (SP2), J3.a28 (SP1), J3.a29 (SP0), J3.b1 (GND), J3.b26 (SP3), J4.a32 (Vin), J4.b32 (Vin), P8.3, P8.4

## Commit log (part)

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2025-03-15 initial
2025-03-16 add 3D and good romboard
2025-03-17 update info
2025-03-17 small update
2025-03-18 update schematic

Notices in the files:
Thor_20_backplane/Thor_20_backplane.kicad_pcb:
(C) 2023 Alvaro Alea Fdz.
Under License
Thor_20_romboard/Thor_20_romboard.kicad_sch:
(C) 2025 Alvaro Alea Fdz
